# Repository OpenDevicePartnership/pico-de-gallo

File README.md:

# Pico de Gallo

A USB bridge that turns a [Raspberry Pi Pico 2](https://www.raspberrypi.com/products/raspberry-pi-pico-2/)
into a host-accessible I²C, SPI, UART, GPIO, PWM, ADC, and 1-Wire interface. Write and test
embedded Rust drivers on your development machine without cross-compiling
or flashing firmware to a target board.

## Overview

Pico de Gallo provides:

- **I²C**: read, write, write-then-read, bus scanning, and transaction batching
- **SPI**: read, write, full-duplex transfer, write-then-read, and transaction batching
- **UART**: read, write, flush, and baud rate configuration
- **GPIO**: digital input/output, edge event monitoring (subscribe/unsubscribe)
- **PWM**: 4-channel PWM output with configurable frequency and duty cycle
- **ADC**: 4 GPIO-based analog inputs (12-bit)
- **1-Wire**: bus reset, read, write, strong pullup, and ROM search (PIO hardware)
- **Configuration**: runtime I²C/SPI/UART/PWM frequency and SPI mode changes

All communication uses [postcard-rpc](https://docs.rs/postcard-rpc) over
USB — a compact, typed, binary RPC protocol.

## Book

The [Pico de Gallo Book](https://balbi.sh/pico-de-gallo/)
covers hardware assembly, firmware flashing, and a step-by-step guide to
writing an embedded device driver using Pico de Gallo.

## Crates

| Crate | Description |
|-------|-------------|
| [`pico-de-gallo-firmware`](crates/pico-de-gallo-firmware) | Embassy-rs firmware for the RP2350 |
| [`pico-de-gallo-lib`](crates/pico-de-gallo-lib) | Async host library (requires tokio) |
| [`pico-de-gallo-hal`](crates/pico-de-gallo-hal) | `embedded-hal` + `embedded-hal-async` implementation |
| [`pico-de-gallo-ffi`](crates/pico-de-gallo-ffi) | C FFI bindings (shared library + header) |
| [`gallo`](crates/pico-de-gallo-app) | CLI application for batch-mode access |
| [`gallo-mcp`](crates/pico-de-gallo-mcp) | MCP server exposing the device to AI agents |
| [`pico-de-gallo-internal`](crates/pico-de-gallo-internal) | Shared wire-protocol types (internal) |

### Firmware

Embassy-rs firmware for the RP2350 that exposes I²C, SPI, UART, and GPIO
peripherals over USB via postcard-rpc endpoints.

Two mutually exclusive board-revision features select the target. `hw-rev2`
(v1.1 and later) is the **default**. `hw-rev1` (v1.0) is **deprecated** — it
stays supported, built in CI, and published as `firmware-rev1.uf2`, with
removal no earlier than 2031-09-01 — and must now be requested explicitly
with `--no-default-features --features hw-rev1`. See
[`crates/pico-de-gallo-firmware/README.md`](crates/pico-de-gallo-firmware/README.md)
for build commands and
[Revisions](https://balbi.sh/pico-de-gallo/hardware/revisions.html) for the
policy.

### Library

Async host-side library wrapping the postcard-rpc transport. Provides
typed methods for every firmware endpoint. Requires the tokio runtime.

### HAL

Implements both `embedded-hal` and `embedded-hal-async` traits — including
`I2c`, `SpiBus`, `SpiDevice`, GPIO digital I/O, delay, and `embedded-io`
Read/Write for UART (0.6 and 0.7, selectable by Cargo feature) — so embedded
device drivers written against those traits can be tested on a host machine
with real hardware attached to the Pico de Gallo.

### App

Command-line tool (`gallo`) for interactive and batch-mode I²C/SPI/UART/GPIO
access. Supports hex, binary, and ASCII output formats.

### FFI

C-compatible shared library wrapping the Rust host library. Generates a
C header via cbindgen. Suitable for integration into C/C++/Python/etc.
projects.

### Internal

Shared wire-protocol crate defining all postcard-rpc endpoints, request
and response types, and constants. Used by both firmware and host crates.

## Zephyr

Zephyr module that lets a Zephyr application running on `native_sim` drive
real I²C, SPI, and GPIO peripherals through the `pico_de_gallo` shield — so
you can write and debug a Zephyr driver on your laptop against real silicon,
without cross-compiling or flashing. See [`zephyr/README.md`](zephyr) for the
full guide; the module is documented there rather than in the book, by the
carve-out recorded in `AGENTS.md` §15.1.

## Hardware

KiCAD schematic and PCB design for a Pico 2 daughter board. The v1.1
board features a single keyed 2x12 shrouded header that routes all 20
firmware signals with on-board I²C pull-ups and ADC input protection.

Additionally, a breadboard adapter is provided in the respective subfolder.
This adapter allows connecting all Pico de Gallo pins to a breadboard
with a single ribbon cable.

## Case

3D-printable snap-fit enclosure (FreeCAD) in two parts — body and lid.

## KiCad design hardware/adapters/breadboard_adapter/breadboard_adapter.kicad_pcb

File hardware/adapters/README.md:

# Adapters

## Breadboard adapter

The `breadboard_adapter` subfolder contains the KiCad schematic
for a breadboard adapter.
This adpaters allows connecting all pins of the Pico de Gallo
to a breadboard with a single ribbon cable.

All pins are labeled according to the Pico de Gallo hardware rev 1.1.
Pin 1 on the ribbon cable connector is indicated on the PCB,
all individual breadboard pins are labeled.

**Required components**:

- 2 x 0.1"/2.54mm pitched single row headers, 12 positions each
- 1 x ribbon cable connector (same type as for Pico de Gallo)

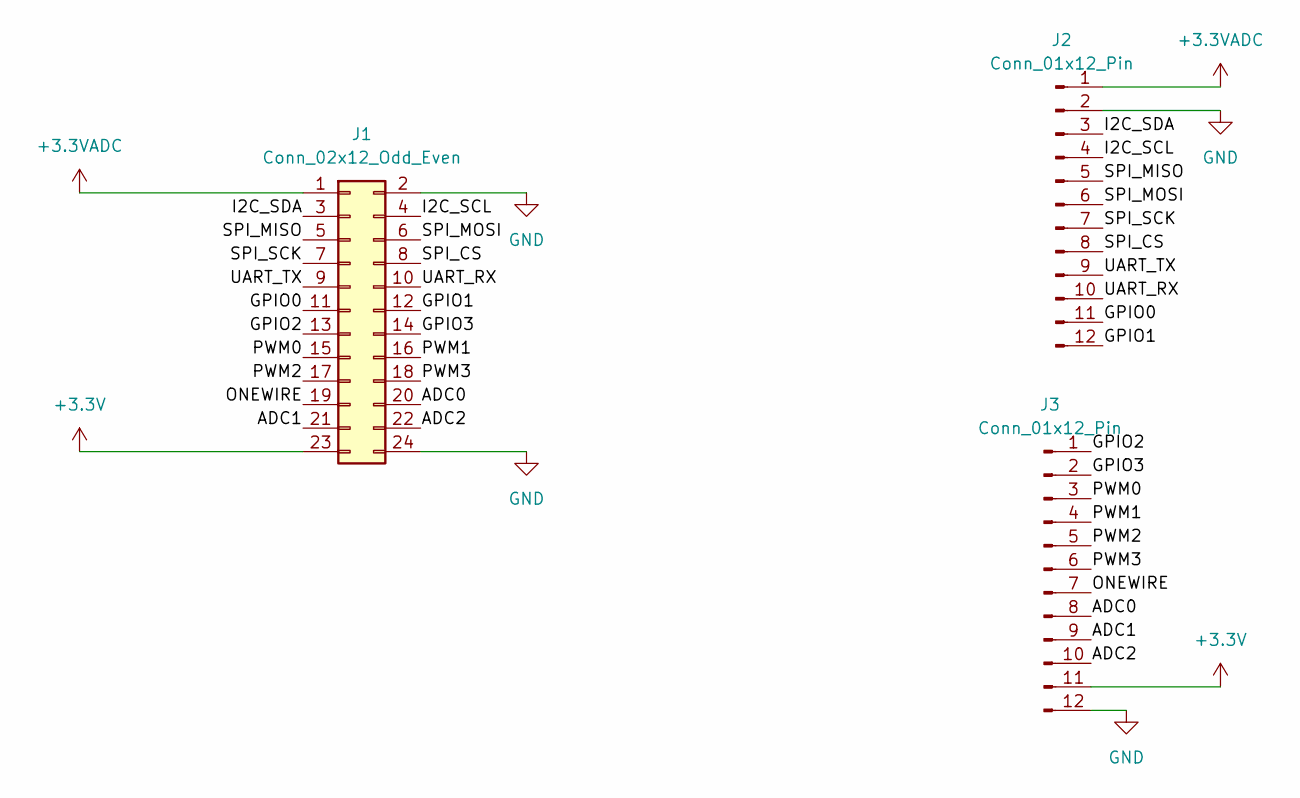
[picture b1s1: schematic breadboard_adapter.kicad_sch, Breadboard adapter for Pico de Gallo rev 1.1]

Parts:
J1: Conn_02x12_Odd_Even; IDC-Header_2x12_P2.54mm_Vertical
J2, J3: Conn_01x12_Pin; PinHeader_1x12_P2.54mm_Vertical

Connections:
+3.3V: J1.23, J3.11
+3.3VADC: J1.1, J2.1
/ADC0: J1.20, J3.8
/ADC1: J1.21, J3.9
/ADC2: J1.22, J3.10
/GPIO0: J1.11, J2.11
/GPIO1: J1.12, J2.12
/GPIO2: J1.13, J3.1
/GPIO3: J1.14, J3.2
/I2C_SCL: J1.4, J2.4
/I2C_SDA: J1.3, J2.3
/ONEWIRE: J1.19, J3.7
/PWM0: J1.15, J3.3
/PWM1: J1.16, J3.4
/PWM2: J1.17, J3.5
/PWM3: J1.18, J3.6
/SPI_CS: J1.8, J2.8
/SPI_MISO: J1.5, J2.5
/SPI_MOSI: J1.6, J2.6
/SPI_SCK: J1.7, J2.7
/UART_RX: J1.10, J2.10
/UART_TX: J1.9, J2.9
GND: J1.2, J1.24, J2.2, J3.12

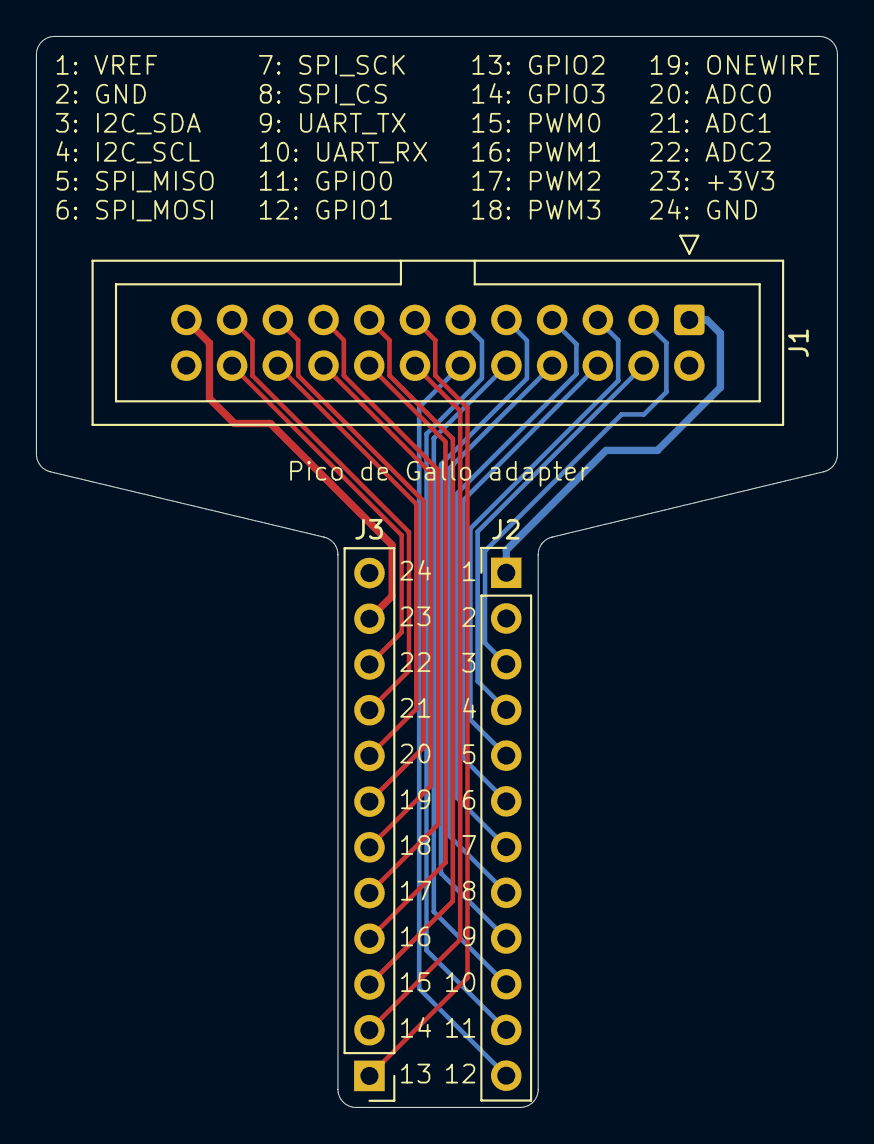
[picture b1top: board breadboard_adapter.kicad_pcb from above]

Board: 4 copper layers, 44.5 x 59.5 mm, 3 parts (0 on the bottom side), 23 nets.

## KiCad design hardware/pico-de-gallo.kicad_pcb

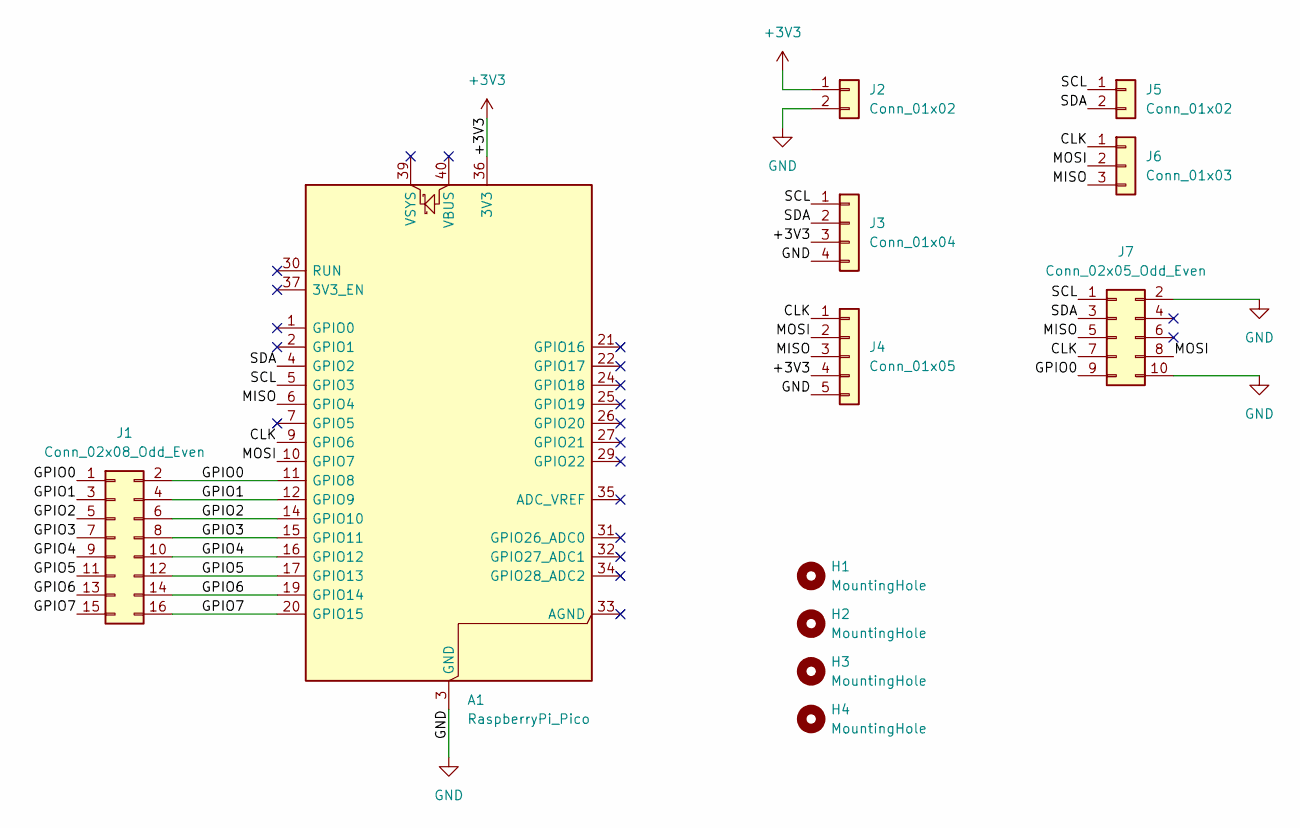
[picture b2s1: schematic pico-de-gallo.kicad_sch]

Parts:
A1: RaspberryPi_Pico; RaspberryPi_Pico_Common_Unspecified
H1, H2, H3, H4: MountingHole; MountingHole_3.2mm_M3
J1: Conn_02x08_Odd_Even; PinHeader_2x08_P2.54mm_Vertical
J2, J5: Conn_01x02; PinHeader_1x02_P2.54mm_Vertical
J3: Conn_01x04; PinSocket_1x04_P2.54mm_Horizontal
J4: Conn_01x05; PinSocket_1x05_P2.54mm_Horizontal
J6: Conn_01x03; PinHeader_1x03_P2.54mm_Vertical
J7: Conn_02x05_Odd_Even; PinHeader_2x05_P2.54mm_Vertical_SMD

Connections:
+3V3: A1.36 (3V3), J2.1, J3.3, J4.4
/CLK: A1.9 (GPIO6), J4.1, J6.1, J7.7
/GPIO0: A1.11 (GPIO8), J1.1, J1.2, J7.9
/GPIO1: A1.12 (GPIO9), J1.3, J1.4
/GPIO2: A1.14 (GPIO10), J1.5, J1.6
/GPIO3: A1.15 (GPIO11), J1.7, J1.8
/GPIO4: A1.16 (GPIO12), J1.9, J1.10
/GPIO5: A1.17 (GPIO13), J1.11, J1.12
/GPIO6: A1.19 (GPIO14), J1.13, J1.14
/GPIO7: A1.20 (GPIO15), J1.15, J1.16
/MISO: A1.6 (GPIO4), J4.3, J6.3, J7.5
/MOSI: A1.10 (GPIO7), J4.2, J6.2, J7.8
/SCL: A1.5 (GPIO3), J3.1, J5.1, J7.1
/SDA: A1.4 (GPIO2), J3.2, J5.2, J7.3
GND: A1.3 (GND), A1.8 (GND), A1.13 (GND), A1.18 (GND), A1.23 (GND), A1.28 (GND), A1.38 (GND), J2.2, J3.4, J4.5, J7.2, J7.10

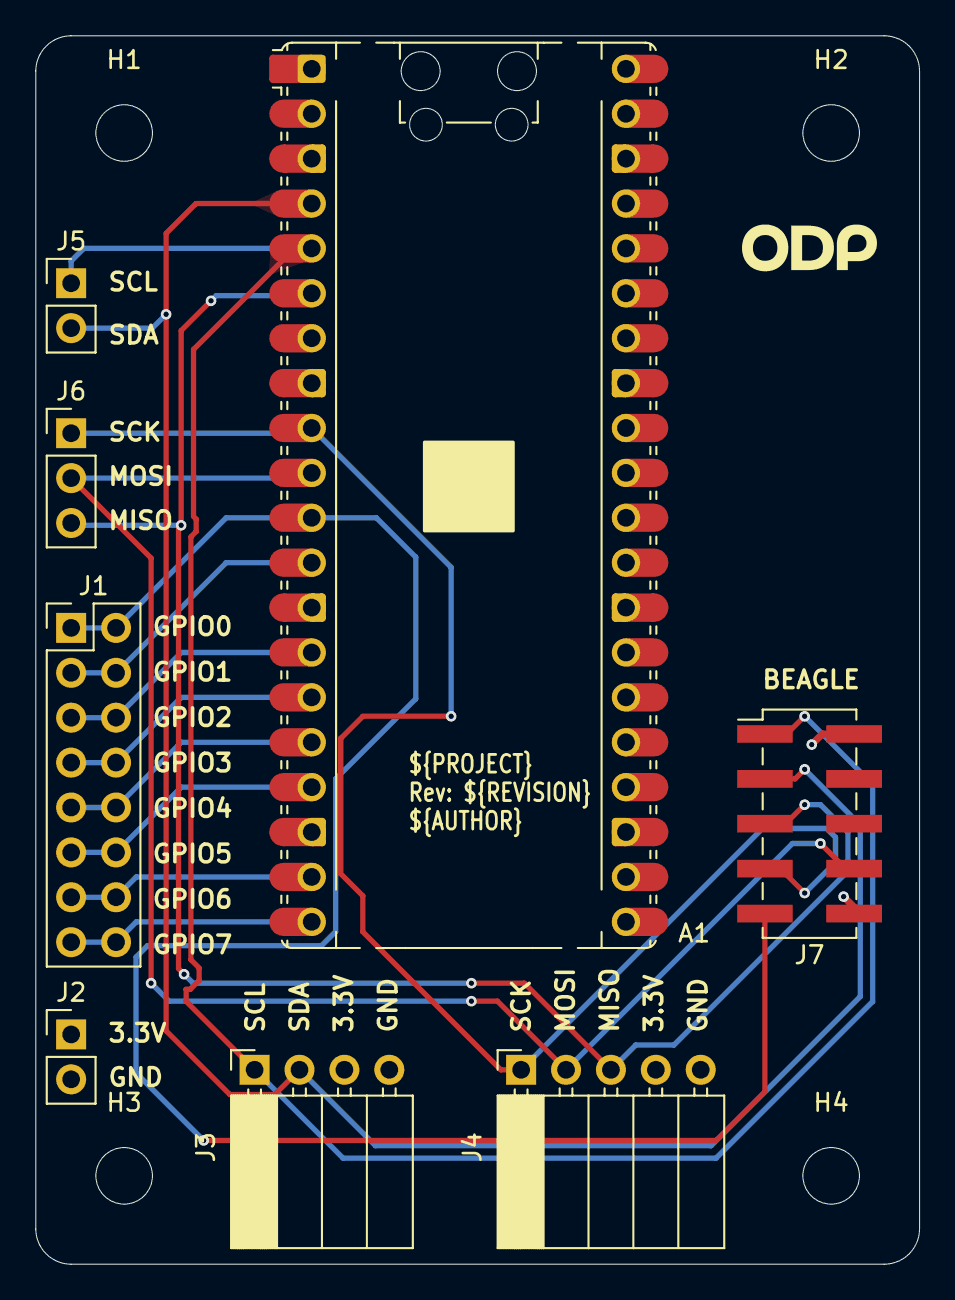
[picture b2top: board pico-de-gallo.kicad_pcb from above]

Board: 4 copper layers, 50.0 x 69.5 mm, 12 parts (0 on the bottom side), 15 nets.

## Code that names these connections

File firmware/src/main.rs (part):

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        p.DMA_CH1,
        embassy_rp::spi::Config::default(),
    );
    let gpio8 = embassy_rp::gpio::Flex::new(p.PIN_8);
    let gpio9 = embassy_rp::gpio::Flex::new(p.PIN_9);
    let gpio10 = embassy_rp::gpio::Flex::new(p.PIN_10);
    let gpio11 = embassy_rp::gpio::Flex::new(p.PIN_11);
    let gpio12 = embassy_rp::gpio::Flex::new(p.PIN_12);
    let gpio13 = embassy_rp::gpio::Flex::new(p.PIN_13);
    let gpio14 = embassy_rp::gpio::Flex::new(p.PIN_14);
    let gpio15 = embassy_rp::gpio::Flex::new(p.PIN_15);

    let gallo = PicoDeGallo::new(
        i2c_bus,
        spi_bus,
        [gpio8, gpio9, gpio10, gpio11, gpio12, gpio13, gpio14, gpio15],
        read_ep,
        write_ep,
    );
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
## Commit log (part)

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2026-06-09 chore(main): release internal 0.6.0
2026-06-09 chore(main): release application 0.7.0
2026-06-09 chore(main): release library 0.6.0
2026-06-09 chore(main): release pyco 0.3.0
2026-06-09 chore(main): release hal 0.6.0
2026-06-09 chore(main): release firmware 0.10.0
2026-06-22 chore(main): release pico-de-gallo libraries

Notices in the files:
hardware/adapters/breadboard_adapter/breadboard_adapter.kicad_pcb:
https://creativecommons.org/licenses/by-sa/4.0
Released under Creative Commons
